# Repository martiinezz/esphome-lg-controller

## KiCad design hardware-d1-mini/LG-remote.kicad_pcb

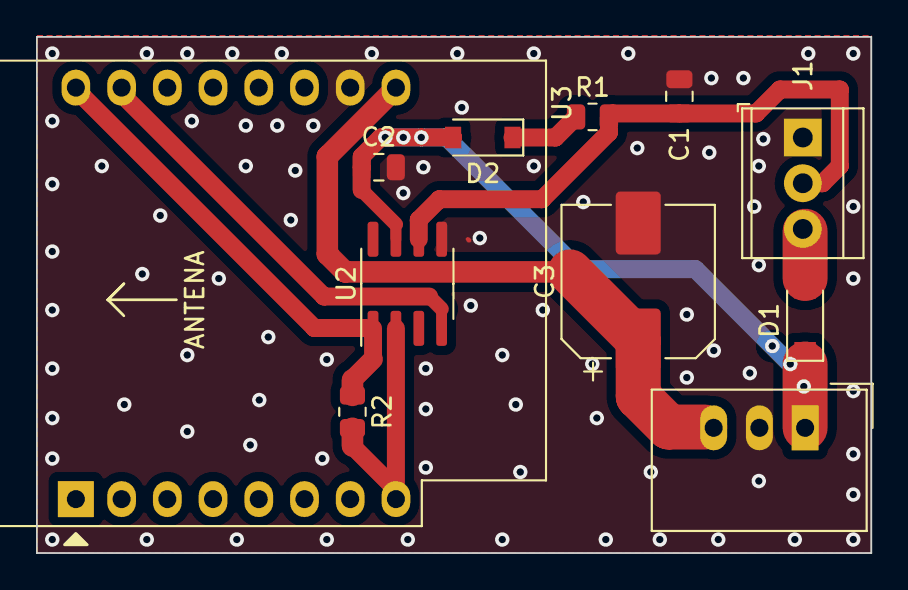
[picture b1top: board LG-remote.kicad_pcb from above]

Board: 2 copper layers, 46.4 x 28.7 mm, 11 parts (0 on the bottom side), 8 nets.

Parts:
C1, C2: C; C_0805_2012Metric
C3: C_Polarized; CP_Elec_8x10
D1, D2: 1N4148W; D_SOD-123
J1: Screw_Terminal_01x03; TerminalBlock_TE_282834-3_1x03_P2.54mm_Horizontal
R1, R2: R; R_0805_2012Metric
U1: TSR_1-2412; Converter_DCDC_TRACO_TSR-1_THT
U2: MCP2021A-xxxxSN; SOIC-8_3.9x4.9mm_P1.27mm
U3: WeMos_D1_mini; WEMOS_D1_mini_light

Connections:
+3V3: R2.2, U2.2 (CS/LWAKE), U3.8 (3V3)
+5V: C3.1, U1.3 (Vout), U3.9 (5V)
+12V: C2.1, D1.1 (K), D1.2 (A), D2.2 (A), J1.3, U1.1 (Vin), U2.7 (VBB)
/LIN: C1.1, J1.2, R1.2, U2.6 (LBUS)
/RXD: R2.1, U2.1 (RXD), U3.16 (TX)
/TXD: U2.4 (TXD), U3.15 (RX)
GND: C1.2, C2.2, C3.2, J1.1, U1.2 (GND), U2.5 (VSS), U3.10 (GND)
unnamed: D2.1 (K), R1.1

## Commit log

2024-09-12 added d1-mini support
2024-09-12 12v line fix
2024-09-12 12v fix
